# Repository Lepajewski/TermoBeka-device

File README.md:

# TermoBeka-device

## Installation Guide

### Windows 10

1. Install [Docker Desktop](https://www.docker.com/products/docker-desktop/). Do not check *Enable integration with my default WSL distro* in settings.

2. Install [Remote Development](https://marketplace.visualstudio.com/items?itemName=ms-vscode-remote.vscode-remote-extensionpack) extenstion in VS Code. Do not check *Execute In WSL* in DEV Container: settings

3. Install [Ubuntu 20.04 LTS](https://apps.microsoft.com/store/detail/ubuntu-20046-lts/9MTTCL66CPXJ)
> Note: kernel version must be higher than `5.10.60.1`, check by `uname -a` on Ubuntu or by `wsl --version` on CMD

4. Make Ubuntu default WSL in CMD: `wsl -l -v` and `wsl --set-default Ubuntu-20.04`

5. Install usbipd in CMD: `winget install usbipd`

6. In Ubuntu run commands:
- `sudo apt-get update && sudo apt-get -qqy upgrade`
- `sudo apt install linux-tools-virtual hwdata`
- `sudo update-alternatives --install /usr/local/bin/usbip usbip $(command -v ls /usr/lib/linux-tools/*/usbip | tail -n1) 20`
- `sudo udevadm control --reload`
- `sudo service udev restart`

7. Plug board to computer (on devkit use UART MicroUSB port).

8. In CMD run:
- `usbipd wsl list`
- `usbipd wsl attach --busid id-id`

Now device should be listed as attached:
- `usbipd wsl list`

> Note: more advanced instructions for steps 6-8 available [here](https://github.com/dorssel/usbipd-win/wiki/WSL-support)

9. Open folder in Dev Container:
- first use: `F1` + `Dev Containers: Rebuild Without Cache and Reopen in Container`
- further use: `F1` + `Dev Containers: Reopen in Container`

10. Wait for PlatrofmIO to setup. Reload window after setup.

11. Finally run in terminal:
- `make all`

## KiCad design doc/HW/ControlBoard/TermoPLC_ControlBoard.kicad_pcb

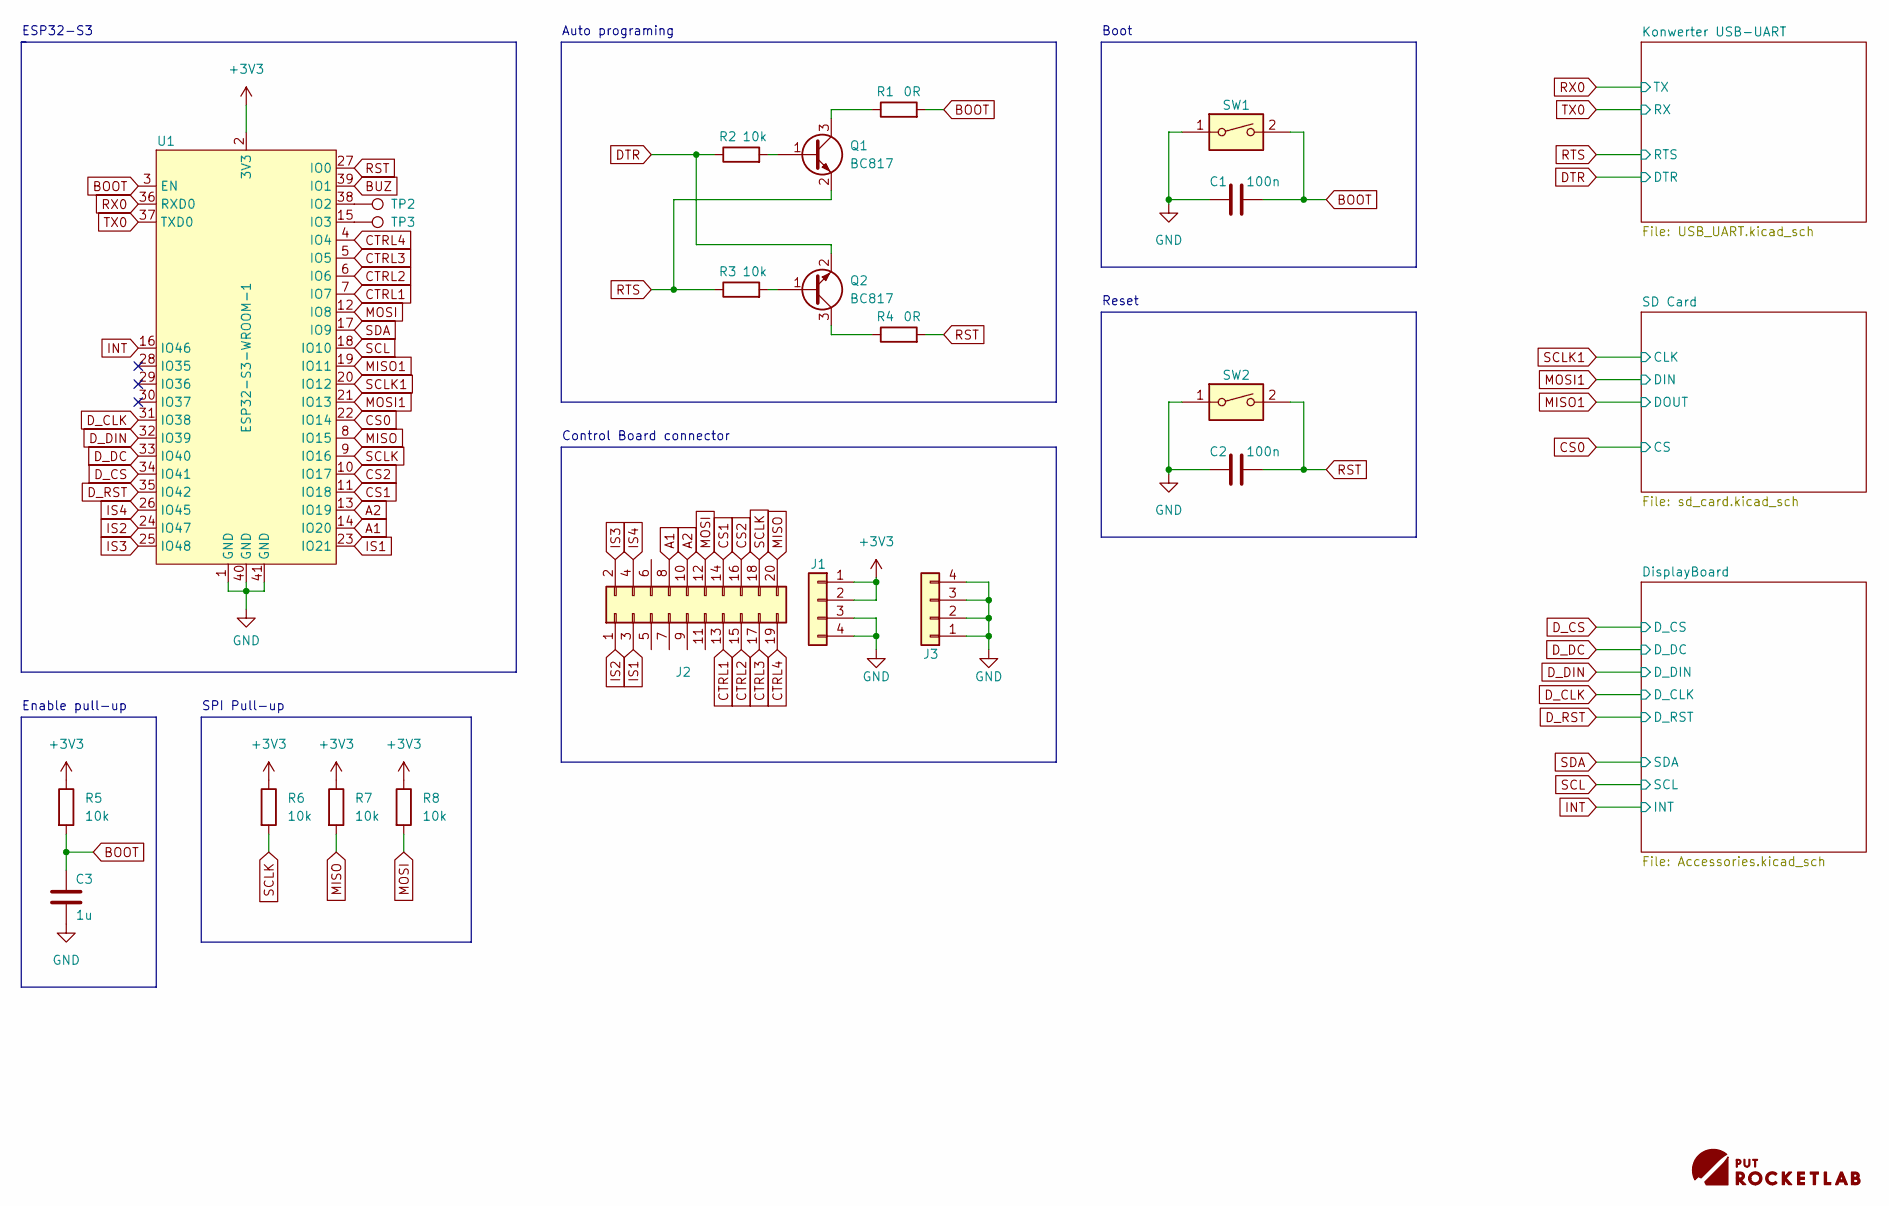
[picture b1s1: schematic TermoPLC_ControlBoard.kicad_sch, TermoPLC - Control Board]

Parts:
C1, C2: 100n; C_0603_1608Metric_Pad1.08x0.95mm_HandSolder
C3: 1u; C_1206_3216Metric_Pad1.33x1.80mm_HandSolder
G1: PutRocketLab_logo_large; PutRocketlab_logo_2_h4mm
J1: Conn_01x04; PinSocket_1x04_P2.54mm_Vertical_SMD_Pin1Left
J2: Conn_02x10_Odd_Even; PinSocket_2x10_P2.54mm_Vertical_SMD
J3: Conn_01x04; PinSocket_1x04_P2.54mm_Vertical_SMD_Pin1Right
Q1, Q2: BC817; SOT-23
R1, R4: 0R; R_0603_1608Metric_Pad0.98x0.95mm_HandSolder
R2, R3, R5, R6, R7, R8: 10k; R_0603_1608Metric_Pad0.98x0.95mm_HandSolder
SW1, SW2: SW_DIP_x01; SW_SPST_FSMSM
TP2, TP3: SolderPoint; TestPoint_Pad_D1.0mm
U1: ESP32-S3-WROOM-1

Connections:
A1: J2.8, U1.14 (IO20)
A2: J2.10, U1.13 (IO19)
BOOT: C1.2, C3.2, R1.2, R5.2, SW1.2, U1.3 (EN)
BUZ: U1.39 (IO1); also elsewhere on the board
CS0: U1.22 (IO14); also elsewhere on the board
CS1: J2.14, U1.11 (IO18)
CS2: J2.16, U1.10 (IO17)
CTRL1: J2.13, U1.7 (IO7)
CTRL2: J2.15, U1.6 (IO6)
CTRL3: J2.17, U1.5 (IO5)
CTRL4: J2.19, U1.4 (IO4)
DTR: Q2.2 (E), R2.1; also elsewhere on the board
D_CLK: U1.31 (IO38); also elsewhere on the board
D_CS: U1.34 (IO41); also elsewhere on the board
D_DC: U1.33 (IO40); also elsewhere on the board
D_DIN: U1.32 (IO39); also elsewhere on the board
D_RST: U1.35 (IO42); also elsewhere on the board
GND: C1.1, C2.1, C3.1, J1.3, J1.4, J3.1, J3.2, J3.3, J3.4, SW1.1, SW2.1, U1.1 (GND), U1.40 (GND), U1.41 (GND); also elsewhere on the board
INT: U1.16 (IO46); also elsewhere on the board
IS1: J2.3, U1.23 (IO21)
IS2: J2.1, U1.24 (IO47)
IS3: J2.2, U1.25 (IO48)
IS4: J2.4, U1.26 (IO45)
MISO: J2.20, R7.2, U1.8 (IO15)
MISO1: U1.19 (IO11); also elsewhere on the board
MOSI: J2.12, R8.2, U1.12 (IO8)
MOSI1: U1.21 (IO13); also elsewhere on the board
unnamed: Q1.1 (B), R2.2
unnamed: Q1.3 (C), R1.1
unnamed: Q2.1 (B), R3.2
unnamed: Q2.3 (C), R4.1
unnamed: TP2.1, U1.38 (IO2)
unnamed: TP3.1, U1.15 (IO3)
RST: C2.2, R4.2, SW2.2, U1.27 (IO0)
RTS: Q1.2 (E), R3.1; also elsewhere on the board
RX0: U1.36 (RXD0); also elsewhere on the board
SCL: U1.18 (IO10); also elsewhere on the board
SCLK: J2.18, R6.2, U1.9 (IO16)
SCLK1: U1.20 (IO12); also elsewhere on the board
SDA: U1.17 (IO9); also elsewhere on the board
TX0: U1.37 (TXD0); also elsewhere on the board

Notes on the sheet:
ESP32-S3
Enable pull-up
Auto programing
Control Board connector
Reset
SPI Pull-up
Boot

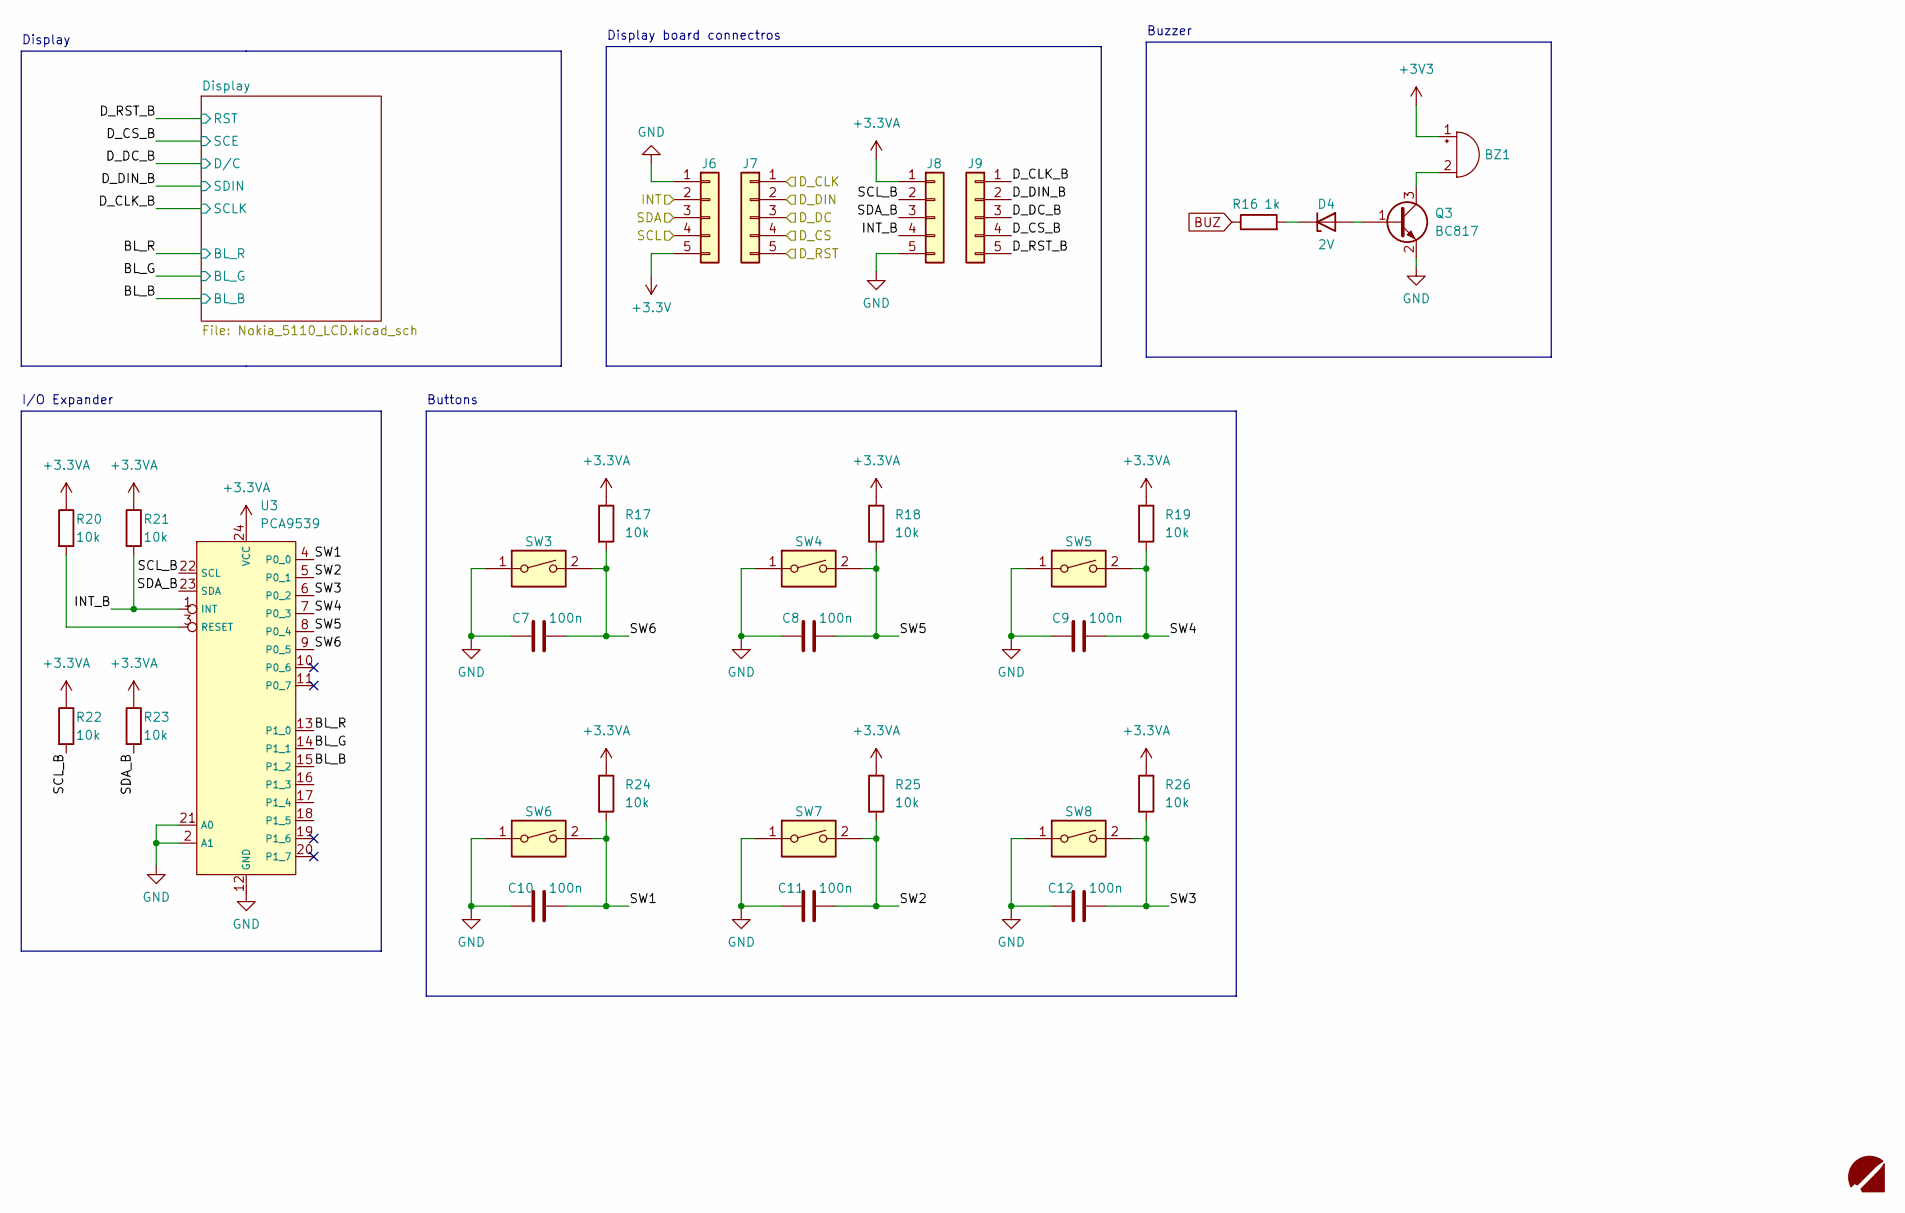
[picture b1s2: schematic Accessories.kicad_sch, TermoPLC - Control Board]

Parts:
BZ1: Buzzer; Buzzer_fi10mm_P5mm
C7, C8, C9, C10, C11, C12: 100n; C_0603_1608Metric_Pad1.08x0.95mm_HandSolder
D4: 2V; D_SOD-123
G2: PutRocketLab_logo_small; PutRocketlab_logo_1_5x5mm
J6: Conn_01x05; PinSocket_1x05_P2.54mm_Vertical_SMD_Pin1Right
J7: Conn_01x05; PinSocket_1x05_P2.54mm_Vertical_SMD_Pin1Left
J8: Conn_01x05; PinHeader_1x05_P2.54mm_Vertical_SMD_Pin1Right
J9: Conn_01x05; PinHeader_1x05_P2.54mm_Vertical_SMD_Pin1Left
Q3: BC817; SOT-23
R16: 1k; R_0603_1608Metric_Pad0.98x0.95mm_HandSolder
R17, R18, R19, R20, R21, R22, R23, R24, R25, R26: 10k; R_0603_1608Metric_Pad0.98x0.95mm_HandSolder
SW3, SW4, SW5, SW6, SW7, SW8: SW_DIP_x01; SW_SPST_PTS645
U3: PCA9539; TSSOP-24_4.4x7.8mm_P0.65mm

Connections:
+3.3VA: J8.1, R17.1, R18.1, R19.1, R20.1, R21.1, R22.1, R23.1, R24.1, R25.1, R26.1, U3.24 (VCC); also elsewhere on the board
/DisplayBoard/BL_B: U3.15 (P1_2); also elsewhere on the board
/DisplayBoard/BL_G: U3.14 (P1_1); also elsewhere on the board
/DisplayBoard/BL_R: U3.13 (P1_0); also elsewhere on the board
/DisplayBoard/D_CLK_B: J9.1; also elsewhere on the board
/DisplayBoard/D_CS_B: J9.4; also elsewhere on the board
/DisplayBoard/D_DC_B: J9.3; also elsewhere on the board
/DisplayBoard/D_DIN_B: J9.2; also elsewhere on the board
/DisplayBoard/D_RST_B: J9.5; also elsewhere on the board
/DisplayBoard/INT_B: J8.4, R21.2, U3.1 (INT)
/DisplayBoard/SCL_B: J8.2, R22.2, U3.22 (SCL)
/DisplayBoard/SDA_B: J8.3, R23.2, U3.23 (SDA)
/DisplayBoard/SW1: C10.2, R24.2, SW6.2, U3.4 (P0_0)
/DisplayBoard/SW2: C11.2, R25.2, SW7.2, U3.5 (P0_1)
/DisplayBoard/SW3: C12.2, R26.2, SW8.2, U3.6 (P0_2)
/DisplayBoard/SW4: C9.2, R19.2, SW5.2, U3.7 (P0_3)
/DisplayBoard/SW5: C8.2, R18.2, SW4.2, U3.8 (P0_4)
/DisplayBoard/SW6: C7.2, R17.2, SW3.2, U3.9 (P0_5)
BUZ: R16.1; also elsewhere on the board
D_CLK: J7.1; also elsewhere on the board
D_CS: J7.4; also elsewhere on the board
D_DC: J7.3; also elsewhere on the board
D_DIN: J7.2; also elsewhere on the board
D_RST: J7.5; also elsewhere on the board
GND: C7.1, C8.1, C9.1, C10.1, C11.1, C12.1, J6.1, J8.5, Q3.2 (E), SW3.1, SW4.1, SW5.1, SW6.1, SW7.1, SW8.1, U3.2 (A1), U3.12 (GND), U3.21 (A0); also elsewhere on the board
INT: J6.2; also elsewhere on the board
unnamed: BZ1.2 (+), Q3.3 (C)
unnamed: D4.1 (K), R16.2
unnamed: D4.2 (A), Q3.1 (B)
unnamed: R20.2, U3.3 (RESET)
SCL: J6.4; also elsewhere on the board
SDA: J6.3; also elsewhere on the board

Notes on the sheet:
Display board connectros
Buttons
Display
I/O Expander
Buzzer

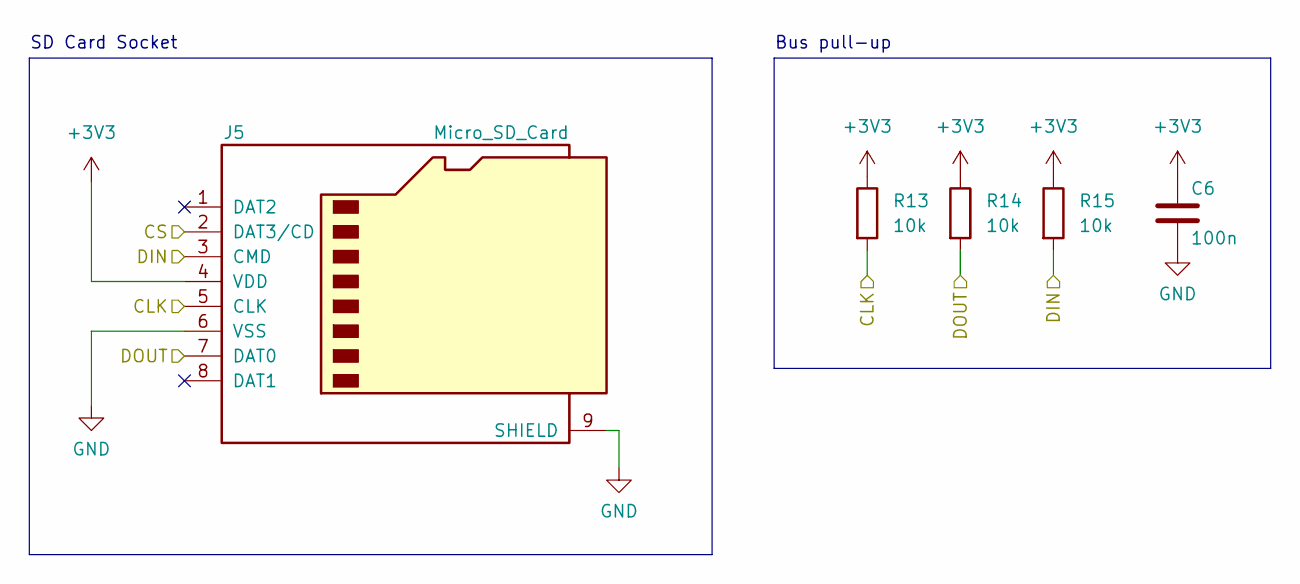
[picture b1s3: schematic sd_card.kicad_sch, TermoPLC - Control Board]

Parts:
C6: 100n; C_0603_1608Metric_Pad1.08x0.95mm_HandSolder
J5: Micro_SD_Card; microSD_HC_Hirose_DM3D-SF
R13, R14, R15: 10k; R_0603_1608Metric_Pad0.98x0.95mm_HandSolder

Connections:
CS0: J5.2 (DAT3/CD); also elsewhere on the board
GND: C6.1, J5.6 (VSS), J5.9 (SHIELD); also elsewhere on the board
MISO1: J5.7 (DAT0), R14.2; also elsewhere on the board
MOSI1: J5.3 (CMD), R15.2; also elsewhere on the board
SCLK1: J5.5 (CLK), R13.2; also elsewhere on the board

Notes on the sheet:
SD Card Socket
Bus pull-up

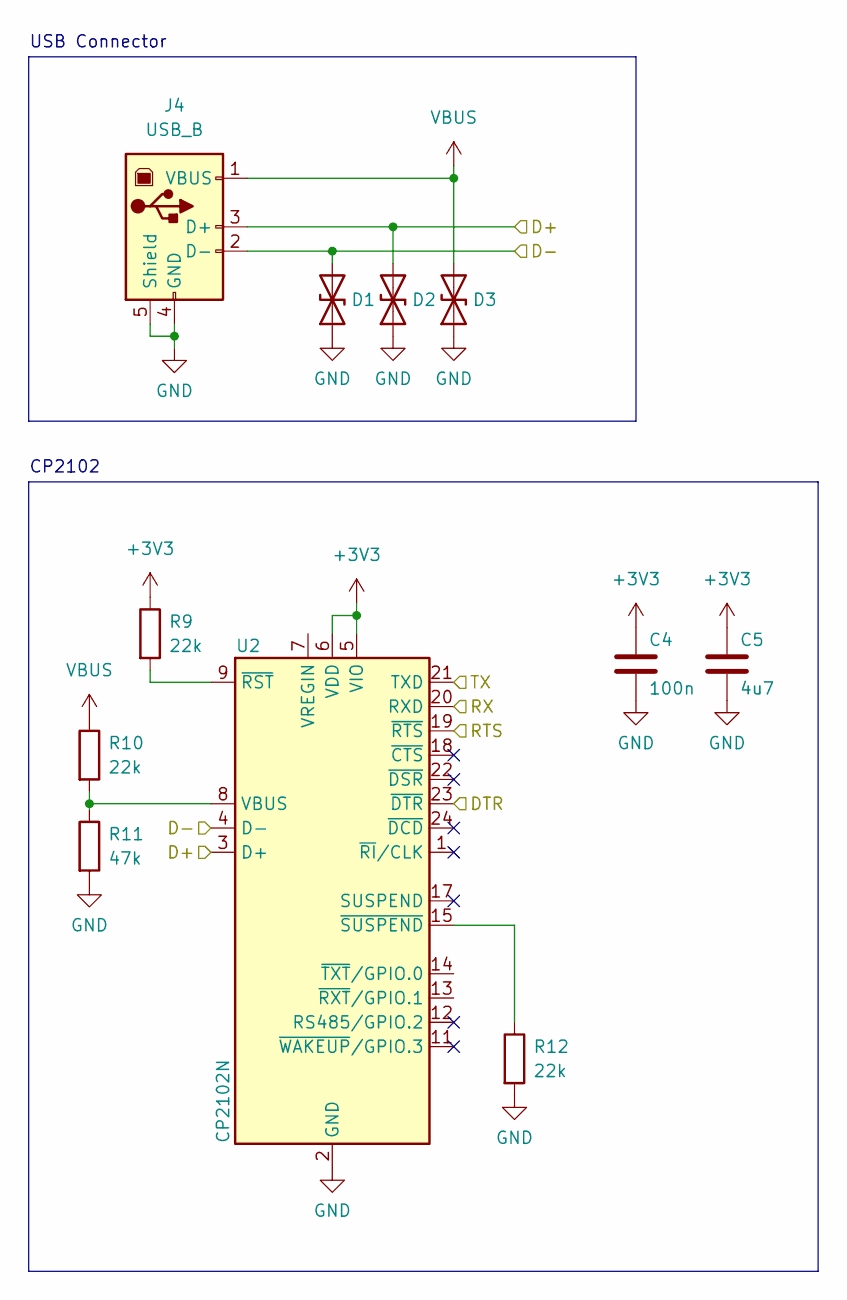
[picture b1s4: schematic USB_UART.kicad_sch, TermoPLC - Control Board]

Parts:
C4: 100n; C_0603_1608Metric_Pad1.08x0.95mm_HandSolder
C5: 4u7; CP_EIA-3216-18_Kemet-A_Pad1.58x1.35mm_HandSolder
D1, D2, D3: D_TVS; D_SOD-923
J4: USB_B; USB_B_OST_USB-B1HSxx_Horizontal
R9, R10, R12: 22k; R_0603_1608Metric_Pad0.98x0.95mm_HandSolder
R11: 47k; R_0603_1608Metric_Pad0.98x0.95mm_HandSolder
U2: CP2102N; QFN-24-1EP_4x4mm_P0.5mm_EP2.6x2.6mm

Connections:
/Konwerter USB-UART/D+: D2.2 (A2), J4.3 (D+), U2.3 (D+)
/Konwerter USB-UART/D-: D1.2 (A2), J4.2 (D-), U2.4 (D-)
DTR: U2.23 (~DTR); also elsewhere on the board
GND: C4.1, C5.2, D1.1 (A1), D2.1 (A1), D3.1 (A1), J4.4 (GND), J4.5 (Shield), R11.2, R12.2, U2.2 (GND), U2.25 (GND); also elsewhere on the board
unnamed: R9.2, U2.9 (~RST)
unnamed: R10.2, R11.1, U2.8 (VBUS)
unnamed: R12.1, U2.15 (~SUSPEND)
RTS: U2.19 (~RTS); also elsewhere on the board
RX0: U2.21 (TXD); also elsewhere on the board
TX0: U2.20 (RXD); also elsewhere on the board
VBUS: D3.2 (A2), J4.1 (VBUS), R10.1

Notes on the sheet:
USB Connector
CP2102

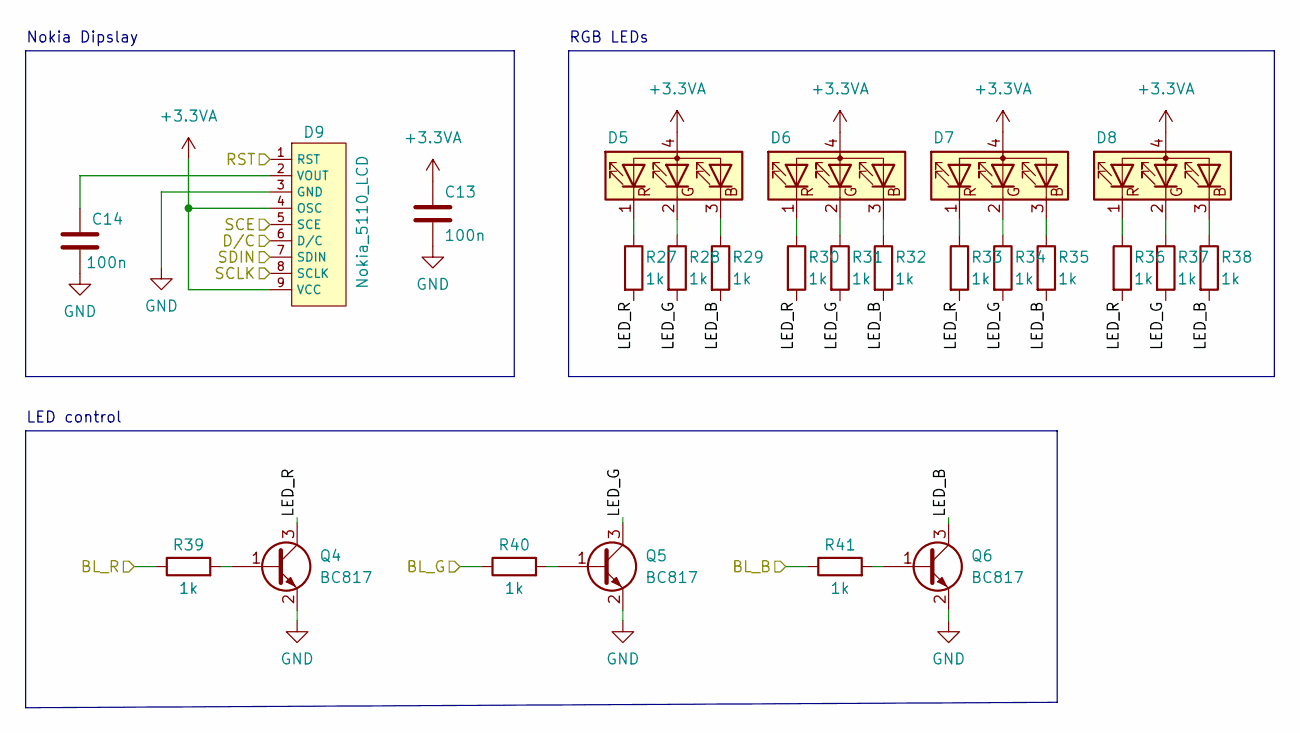
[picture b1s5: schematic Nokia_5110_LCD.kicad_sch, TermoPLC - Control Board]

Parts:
C13, C14: 100n; C_0603_1608Metric_Pad1.08x0.95mm_HandSolder
D5, D6, D7, D8: LED_RGBA; LED_Lumex_SML-LX0404SIUPGUSB
D9: Nokia_5110_LCD; Raw_Nokia_5110_LCD
Q4, Q5, Q6: BC817; SOT-23
R27, R28, R29, R30, R31, R32, R33, R34, R35, R36, R37, R38, R39, R40, R41: 1k; R_0603_1608Metric_Pad0.98x0.95mm_HandSolder

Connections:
+3.3VA: C13.2, D5.4 (A), D6.4 (A), D7.4 (A), D8.4 (A), D9.4 (OSC), D9.9 (VCC); also elsewhere on the board
/DisplayBoard/BL_B: R41.1; also elsewhere on the board
/DisplayBoard/BL_G: R40.1; also elsewhere on the board
/DisplayBoard/BL_R: R39.1; also elsewhere on the board
/DisplayBoard/D_CLK_B: D9.8 (SCLK); also elsewhere on the board
/DisplayBoard/D_CS_B: D9.5 (SCE); also elsewhere on the board
/DisplayBoard/D_DC_B: D9.6 (D/C); also elsewhere on the board
/DisplayBoard/D_DIN_B: D9.7 (SDIN); also elsewhere on the board
/DisplayBoard/D_RST_B: D9.1 (RST); also elsewhere on the board
/DisplayBoard/Display/LED_B: Q6.3 (C), R29.2, R32.2, R35.2, R38.2
/DisplayBoard/Display/LED_G: Q5.3 (C), R28.2, R31.2, R34.2, R37.2
/DisplayBoard/Display/LED_R: Q4.3 (C), R27.2, R30.2, R33.2, R36.2
GND: C13.1, C14.1, D9.3 (GND), Q4.2 (E), Q5.2 (E), Q6.2 (E); also elsewhere on the board
unnamed: C14.2, D9.2 (VOUT)
unnamed: D5.1 (RK), R27.1
unnamed: D5.2 (GK), R28.1
unnamed: D5.3 (BK), R29.1
unnamed: D6.1 (RK), R30.1
unnamed: D6.2 (GK), R31.1
unnamed: D6.3 (BK), R32.1
unnamed: D7.1 (RK), R33.1
unnamed: D7.2 (GK), R34.1
unnamed: D7.3 (BK), R35.1
unnamed: D8.1 (RK), R36.1
unnamed: D8.2 (GK), R37.1
unnamed: D8.3 (BK), R38.1
unnamed: Q4.1 (B), R39.2
unnamed: Q5.1 (B), R40.2
unnamed: Q6.1 (B), R41.2

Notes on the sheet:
RGB LEDs
LED control
Nokia Dipslay

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
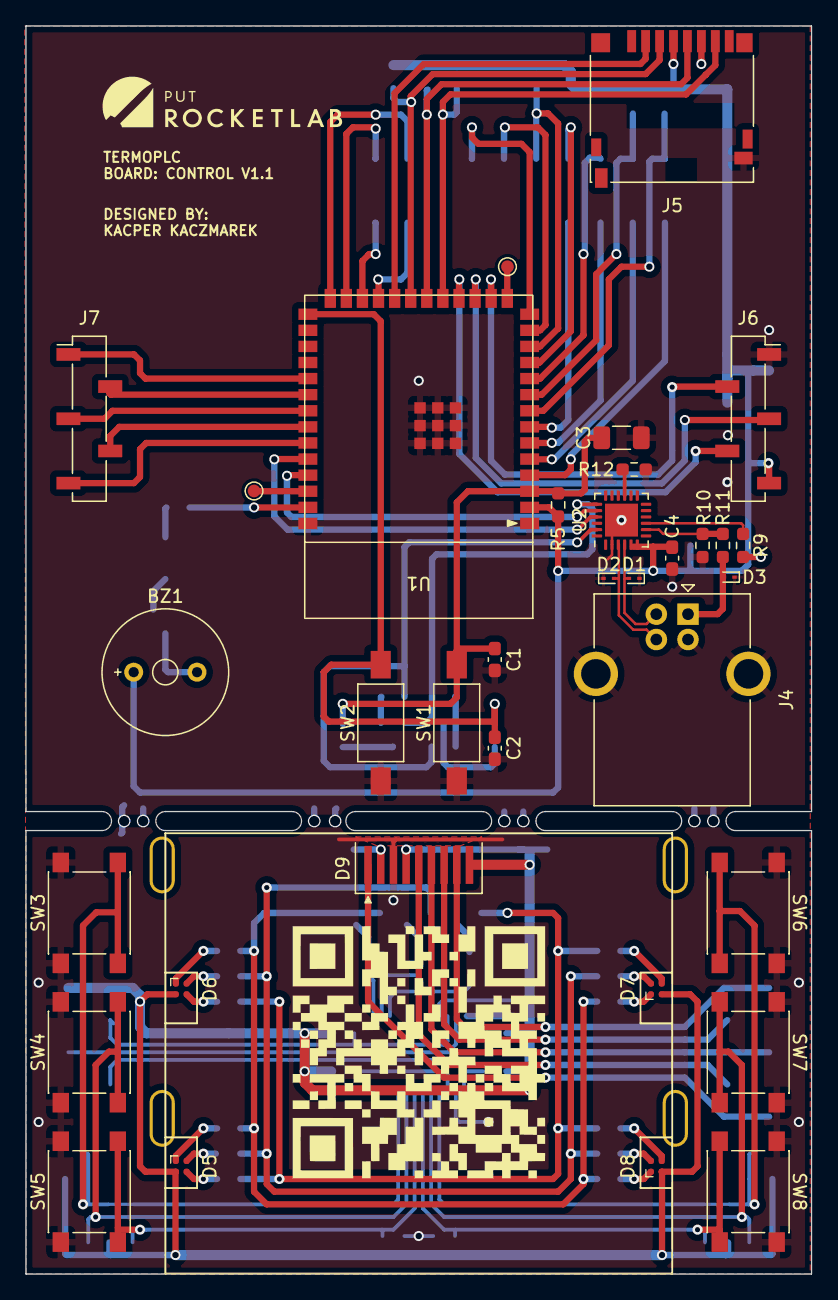
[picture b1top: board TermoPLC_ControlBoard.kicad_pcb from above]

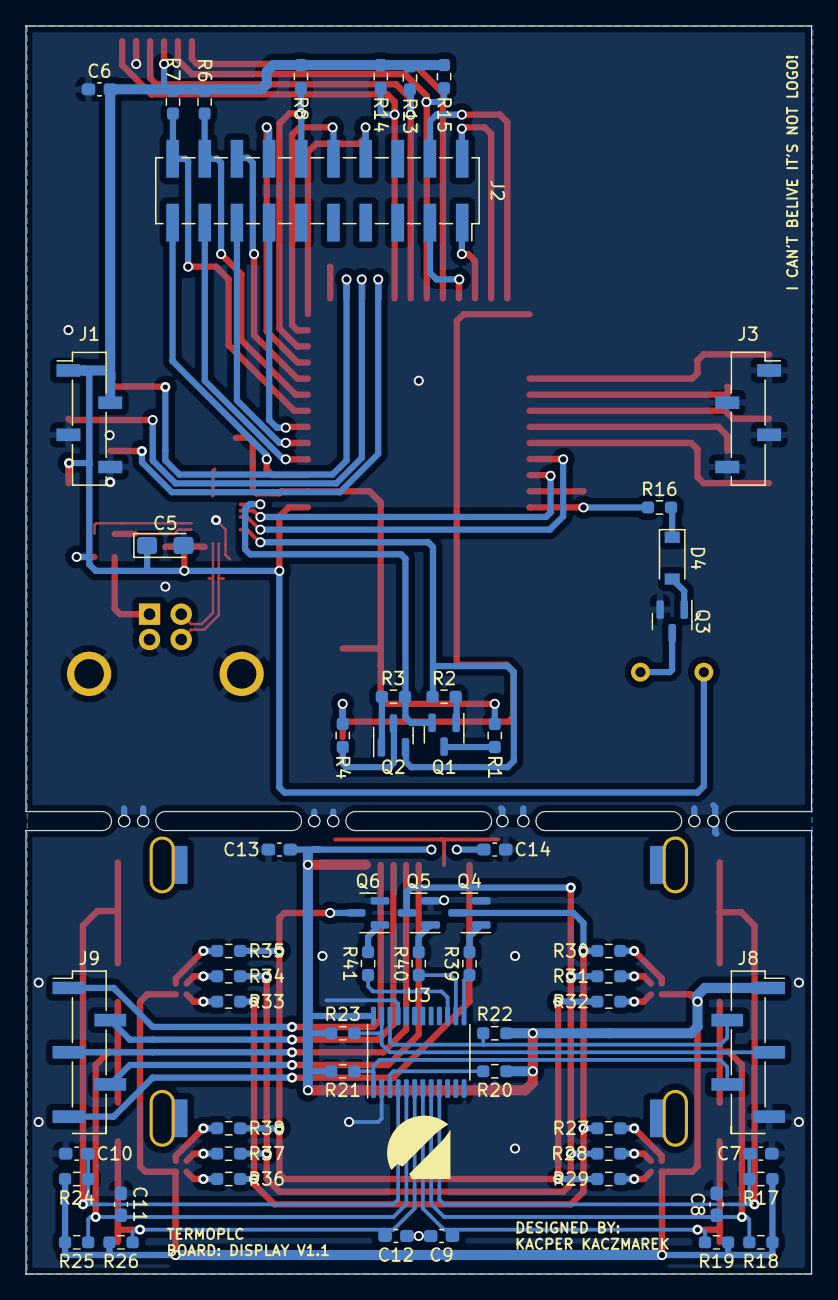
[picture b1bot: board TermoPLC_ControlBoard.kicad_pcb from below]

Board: 2 copper layers, 62.0 x 98.5 mm, 95 parts (60 on the bottom side), 89 nets.

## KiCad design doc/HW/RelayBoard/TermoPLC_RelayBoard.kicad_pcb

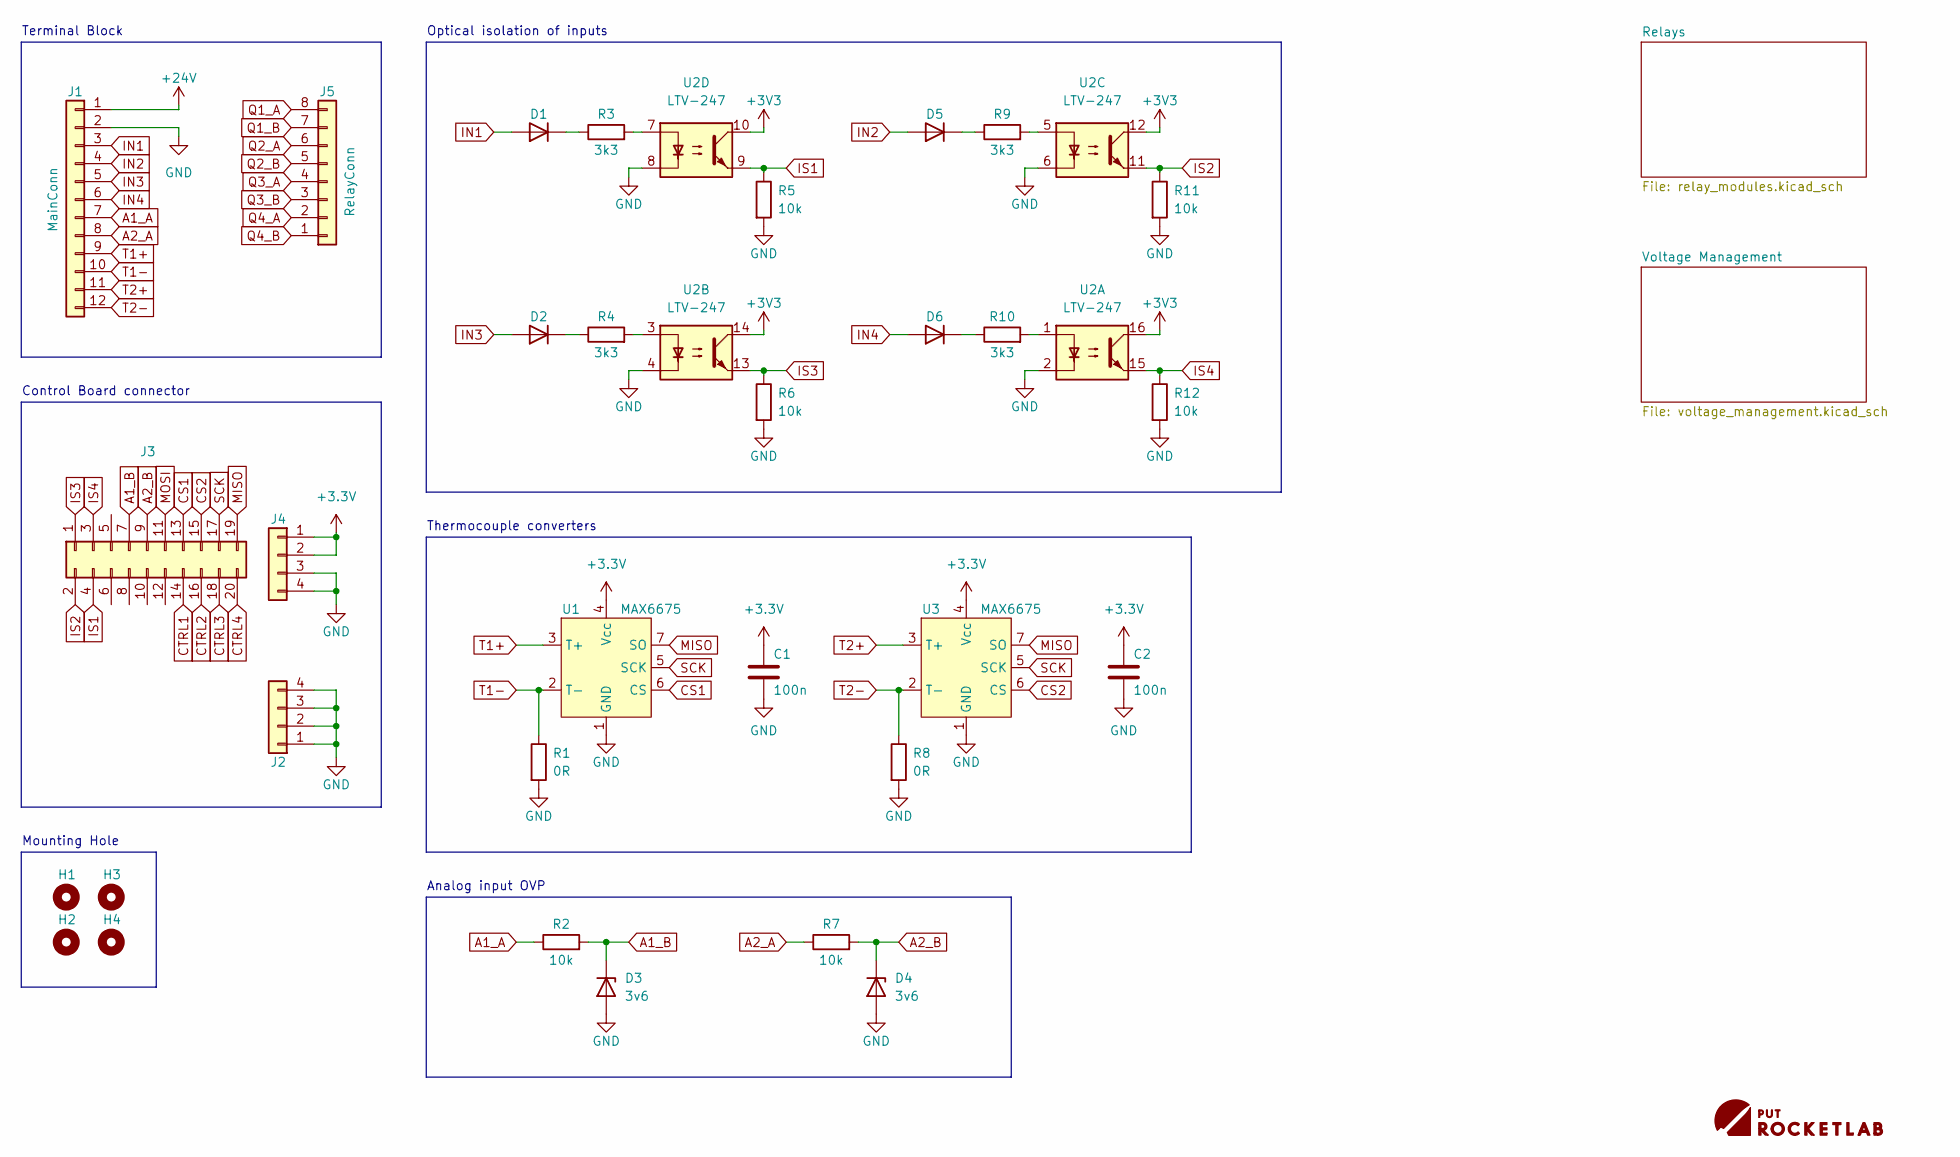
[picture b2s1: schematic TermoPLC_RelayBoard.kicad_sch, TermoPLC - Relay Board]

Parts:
C1, C2: 100n; C_0603_1608Metric_Pad1.08x0.95mm_HandSolder
D1, D2, D5, D6: D; D_MiniMELF
D3, D4: 3v6; D_SOD-123
G1: PutRocketLab_logo_large; PutRocketlab_logo_2_h4mm
H1, H2, H3, H4: M3; MountingHole_3.2mm_M3
J1: MainConn; TerminalBlock_RND_205-00055_1x12_P5.00mm_Horizontal
J2, J4: Conn_01x04; PinSocket_1x04_P2.54mm_Vertical
J3: Conn_02x10_Odd_Even; PinSocket_2x10_P2.54mm_Vertical
J5: RelayConn; TerminalBlock_RND_205-00073_1x08_P7.50mm_Horizontal
R1, R8: 0R; R_0603_1608Metric_Pad0.98x0.95mm_HandSolder
R2, R5, R6, R7, R11, R12: 10k; R_0603_1608Metric_Pad0.98x0.95mm_HandSolder
R3, R4, R9, R10: 3k3; R_1206_3216Metric_Pad1.30x1.75mm_HandSolder
U1, U3: MAX6675; PowerIntegrations_SO-8
U2: LTV-247; SOP-16_4.4x10.4mm_P1.27mm

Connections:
+24V: J1.1; also elsewhere on the board
A1_A: J1.7, R2.1
A1_B: D3.1 (K), J3.7, R2.2
A2_A: J1.8, R7.1
A2_B: D4.1 (K), J3.9, R7.2
CS1: J3.13, U1.6 (CS)
CS2: J3.15, U3.6 (CS)
CTRL1: J3.14; also elsewhere on the board
CTRL2: J3.16; also elsewhere on the board
CTRL3: J3.18; also elsewhere on the board
CTRL4: J3.20; also elsewhere on the board
GND: C1.2, C2.2, D3.2 (A), D4.2 (A), J1.2, J2.1, J2.2, J2.3, J2.4, J4.3, J4.4, R1.2, R5.2, R6.2, R8.2, R11.2, R12.2, U1.1 (GND), U2.2, U2.4, U2.6, U2.8, U3.1 (GND); also elsewhere on the board
IN1: D1.2 (A), J1.3
IN2: D5.2 (A), J1.4
IN3: D2.2 (A), J1.5
IN4: D6.2 (A), J1.6
IS1: J3.4, R5.1, U2.9
IS2: J3.2, R11.1, U2.11
IS3: J3.1, R6.1, U2.13
IS4: J3.3, R12.1, U2.15
MISO: J3.19, U1.7 (SO), U3.7 (SO)
MOSI: J3.11
unnamed: D1.1 (K), R3.1
unnamed: D2.1 (K), R4.1
unnamed: D5.1 (K), R9.1
unnamed: D6.1 (K), R10.1
unnamed: R3.2, U2.7
unnamed: R4.2, U2.3
unnamed: R9.2, U2.5
unnamed: R10.2, U2.1
Q1_A: J5.8; also elsewhere on the board
Q1_B: J5.7; also elsewhere on the board
Q2_A: J5.6; also elsewhere on the board
Q2_B: J5.5; also elsewhere on the board
Q3_A: J5.4; also elsewhere on the board
Q3_B: J5.3; also elsewhere on the board
Q4_A: J5.2; also elsewhere on the board
Q4_B: J5.1; also elsewhere on the board
SCK: J3.17, U1.5 (SCK), U3.5 (SCK)
T1+: J1.9, U1.3 (T+)
T1-: J1.10, R1.1, U1.2 (T-)
T2+: J1.11, U3.3 (T+)
T2-: J1.12, R8.1, U3.2 (T-)

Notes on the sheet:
Terminal Block
Analog input OVP
Control Board connector
Thermocouple converters
Mounting Hole
Optical isolation of inputs

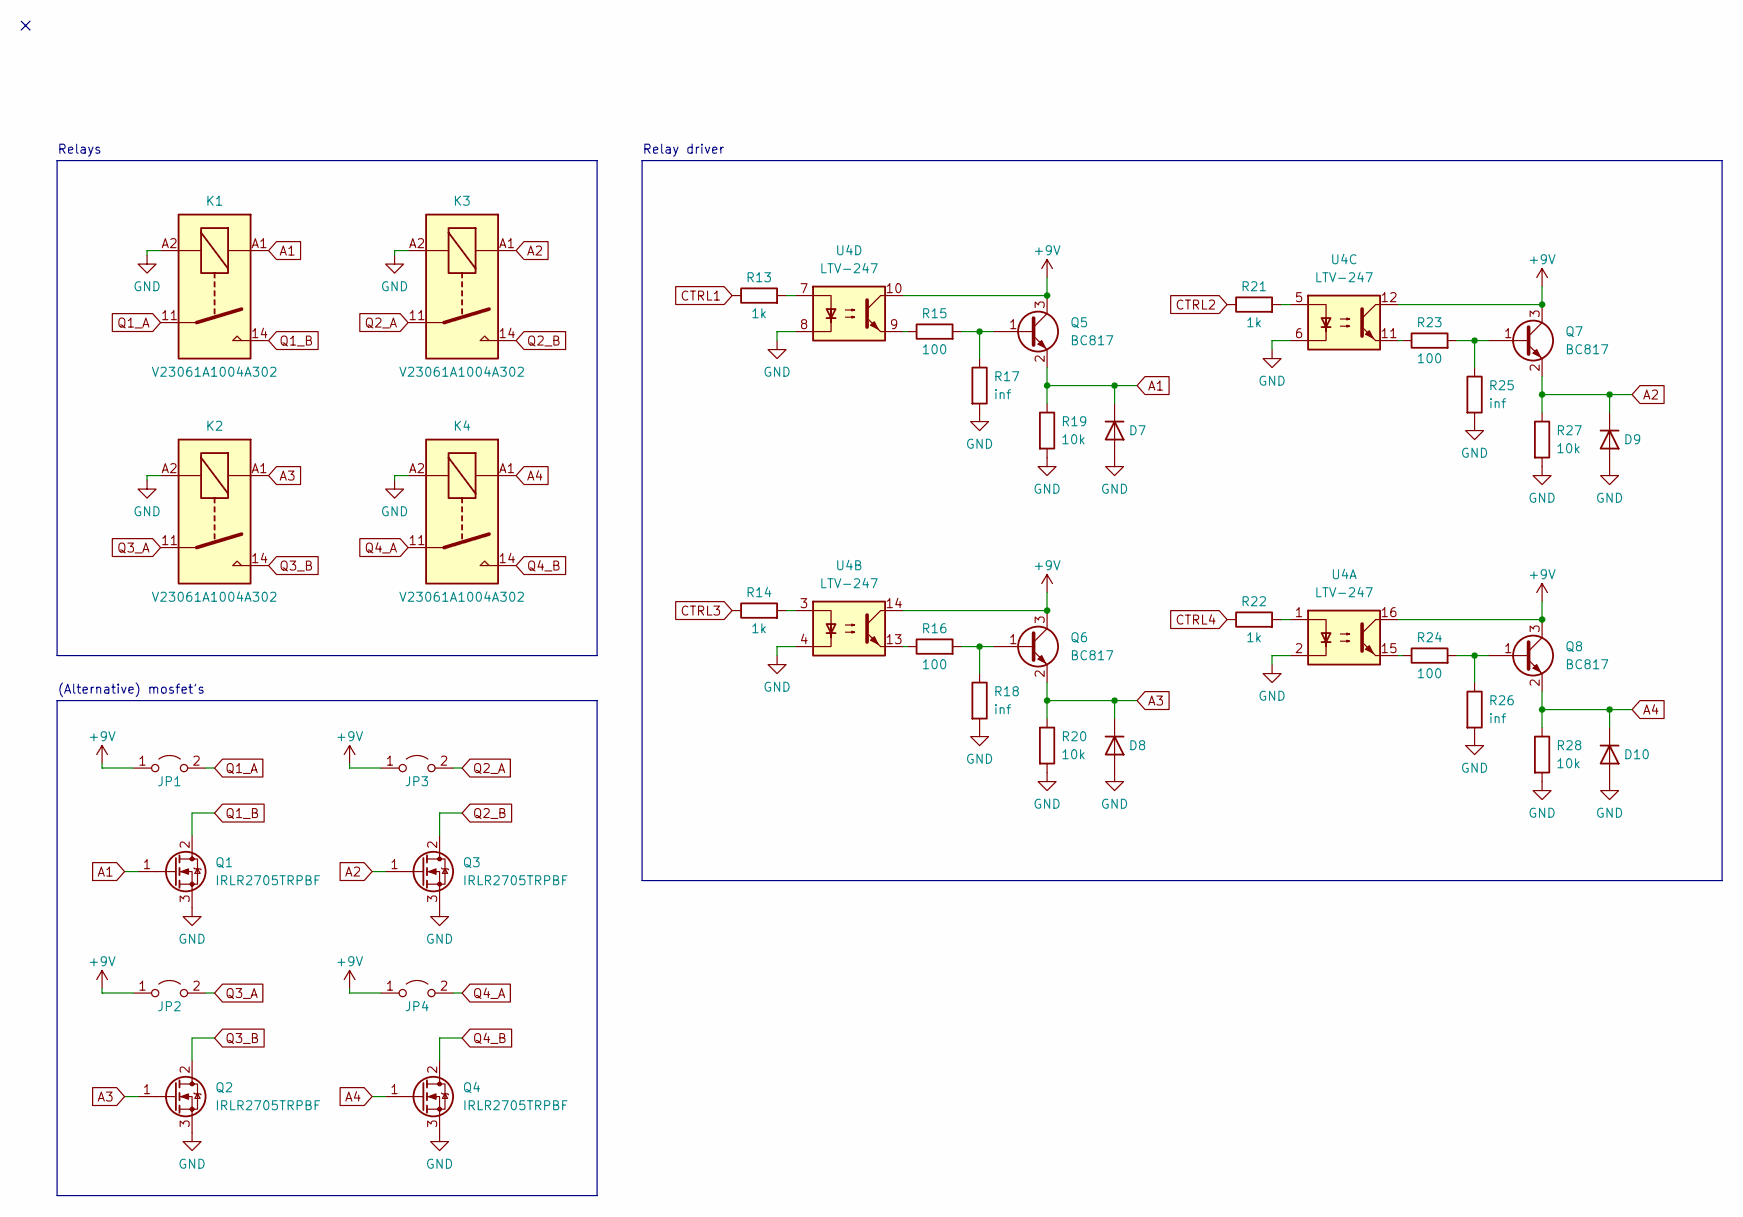
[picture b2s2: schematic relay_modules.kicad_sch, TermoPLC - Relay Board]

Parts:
D7, D8, D9, D10: D; D_MiniMELF
JP1, JP2, JP3, JP4: Shorted in mosfet mode; R_0603_1608Metric_Pad0.98x0.95mm_HandSolder
K1, K2, K3, K4: V23061A1004A302; V23061-A1004-A302
Q1, Q2, Q3, Q4: IRLR2705TRPBF; TO-252-2
Q5, Q6, Q7, Q8: BC817; SOT-23
R13, R14, R21, R22: 1k; R_0603_1608Metric_Pad0.98x0.95mm_HandSolder
R15, R16, R23, R24: 100; R_0603_1608Metric_Pad0.98x0.95mm_HandSolder
R17, R18, R25, R26: inf; R_0603_1608Metric_Pad0.98x0.95mm_HandSolder
R19, R20, R27, R28: 10k; R_0603_1608Metric_Pad0.98x0.95mm_HandSolder
U4: LTV-247; SOP-16_4.4x10.4mm_P1.27mm

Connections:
+9V: JP1.1 (A), JP2.1 (A), JP3.1 (A), JP4.1 (A), Q5.3 (C), Q6.3 (C), Q7.3 (C), Q8.3 (C), U4.10, U4.12, U4.14, U4.16; also elsewhere on the board
A1: D7.1 (K), K1.A1, Q1.1 (G), Q5.2 (E), R19.1
A2: D9.1 (K), K3.A1, Q3.1 (G), Q7.2 (E), R27.1
A3: D8.1 (K), K2.A1, Q2.1 (G), Q6.2 (E), R20.1
A4: D10.1 (K), K4.A1, Q4.1 (G), Q8.2 (E), R28.1
CTRL1: R13.1; also elsewhere on the board
CTRL2: R21.1; also elsewhere on the board
CTRL3: R14.1; also elsewhere on the board
CTRL4: R22.1; also elsewhere on the board
GND: D7.2 (A), D8.2 (A), D9.2 (A), D10.2 (A), K1.A2, K2.A2, K3.A2, K4.A2, Q1.3 (S), Q2.3 (S), Q3.3 (S), Q4.3 (S), R17.2, R18.2, R19.2, R20.2, R25.2, R26.2, R27.2, R28.2, U4.2, U4.4, U4.6, U4.8; also elsewhere on the board
unnamed: Q5.1 (B), R15.2, R17.1
unnamed: Q6.1 (B), R16.2, R18.1
unnamed: Q7.1 (B), R23.2, R25.1
unnamed: Q8.1 (B), R24.2, R26.1
unnamed: R13.2, U4.7
unnamed: R14.2, U4.3
unnamed: R15.1, U4.9
unnamed: R16.1, U4.13
unnamed: R21.2, U4.5
unnamed: R22.2, U4.1
unnamed: R23.1, U4.11
unnamed: R24.1, U4.15
Q1_A: JP1.2 (B), K1.11; also elsewhere on the board
Q1_B: K1.14, Q1.2 (D); also elsewhere on the board
Q2_A: JP3.2 (B), K3.11; also elsewhere on the board
Q2_B: K3.14, Q3.2 (D); also elsewhere on the board
Q3_A: JP2.2 (B), K2.11; also elsewhere on the board
Q3_B: K2.14, Q2.2 (D); also elsewhere on the board
Q4_A: JP4.2 (B), K4.11; also elsewhere on the board
Q4_B: K4.14, Q4.2 (D); also elsewhere on the board

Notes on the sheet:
Relay driver
(Alternative) mosfet's
Relays
